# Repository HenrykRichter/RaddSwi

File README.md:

# RaddSwi
This project contains the design files of an automatic MonitorSwitch add-on for the Amiga Flickerfixer [Multifix AGA](https://gitlab.com/MHeinrichs/multifix-aga) by Matthias Heinrichs.
The key idea of using SPDTs for switching between VGA inputs was borrowed from the Ratte Monitor switch by Andre Pfeiffer (hence the title of this project). Also originating from the work of Andre Pfeiffer is the software part. His Amiga utility called switchcontrol is re-used in slightly modified form for this monitor switcher.

Conceptually, a monitor switch is used on Amiga to merge the outputs of Amiga native video (or a Flickerfixer/Scandoubler) and an RTG graphics card to enable the use of a single monitor cable, where the relevant signal is passed through to the monitor. For that purpose, a combination of hard- and software is necessary. 

By default, RaddSwi will pass the native Amiga signal to the monitor. As soon as the software utility detects an active RTG screen, it will generate a signal that instructs the monitorswitch to patch the RTG outputs from the graphics card through. Please see below for differences between the classic Ratte Switch and this approach.

The output of the multiplexed signal can be obtained from the regular VGA connector of the Multifix AGA.

## Hardware notes 
The obvious prerequisite for this solution is a working Multifix AGA. 
This project consists of two PCBs, the switch and a PLCC44 adapter for the switching input signal. 
The PLCC44 adapter for U300 in Amiga 4000 computers requires an 1x4 angled pin strip and an SMD PLCC44 socket. For operation in Amiga2000/3000 computers, please refer to my other projects for a DIP CIAB Adapter.

The components for the switch are listed below:
- 1x STM AV340TTR (Mouser: 511-STMAV340TTR)
- 2x TS5A3159 (Mouser: 595-TS5A3159QDBVRQ1)
- 1x 2x5 R/A shrouded pin header .1" (Mouser: 798-HIF3FC10PA254DS1)
- 1x 2x7 Socket strip vertical .1"
- 1x 10k 0603
- 2x FB 120Ohms@100 MHz
- 3x 100nF 0603
- 1x 10uF 0805
- 1x 1x3 R/A pin header

The switch is supposed to be mounted upside-down on the 2x7 pin strip of the Multifix AGA. Three additional connections are required: 5V, GND and the switch signal. Probably the best option for a stable power supply is the programming header of the MultiFix AGA (JTAG), where Pin 2 carries GND and Pin 4 +5V. The Switch signal connects to CIAB, either DTR or (classic RatteSwitch) CTS.

I'd suggest to go for DTR instead of CTS, since this way is friendlier to the ICs involved. CTS is normally set to input in Amiga computers, where the relevant signal from the serial port is going through an MC1489. Using that pin as output on the CIA will have the CSG8520 pin 8 and the MC1489 pin 6 at odds with each other. That's why this project uses DTR as switching signal, whose state is available both internally (CIAB) and externally (RS232 DB25).

The third piece of hardware needed is the connection between the RTG graphics card and the switcher. The 2x5 connector on raddswi will need analog R,G,B,HSync,VSync and AGND supplied. A typical generic approach is to adapt a short VGA cable for this purpose. Please have a look into the Pics/ subfolder, where the respective connections between a VGA cable and the 2x5 input header are depicted.

## Software notes
Select the SwitchControl binary matching your connection (DTR or CTS), copy it to C: on your Amiga's harddrive and modify your s:user-startup or s:startup-sequence. The only addition to one of the files (preferably s:user-startup) is a line that reads

C:SwitchControl

Important: SwitchControl needs to be started after the Monitor driver(s), thus in s:user-startup or late in s:startup-sequence. 

## Pictures

## License
The PCB, it's design files and all support code are licensed as [CC BY NC SA](https://creativecommons.org/licenses/by-nc-sa/4.0/deed.en).

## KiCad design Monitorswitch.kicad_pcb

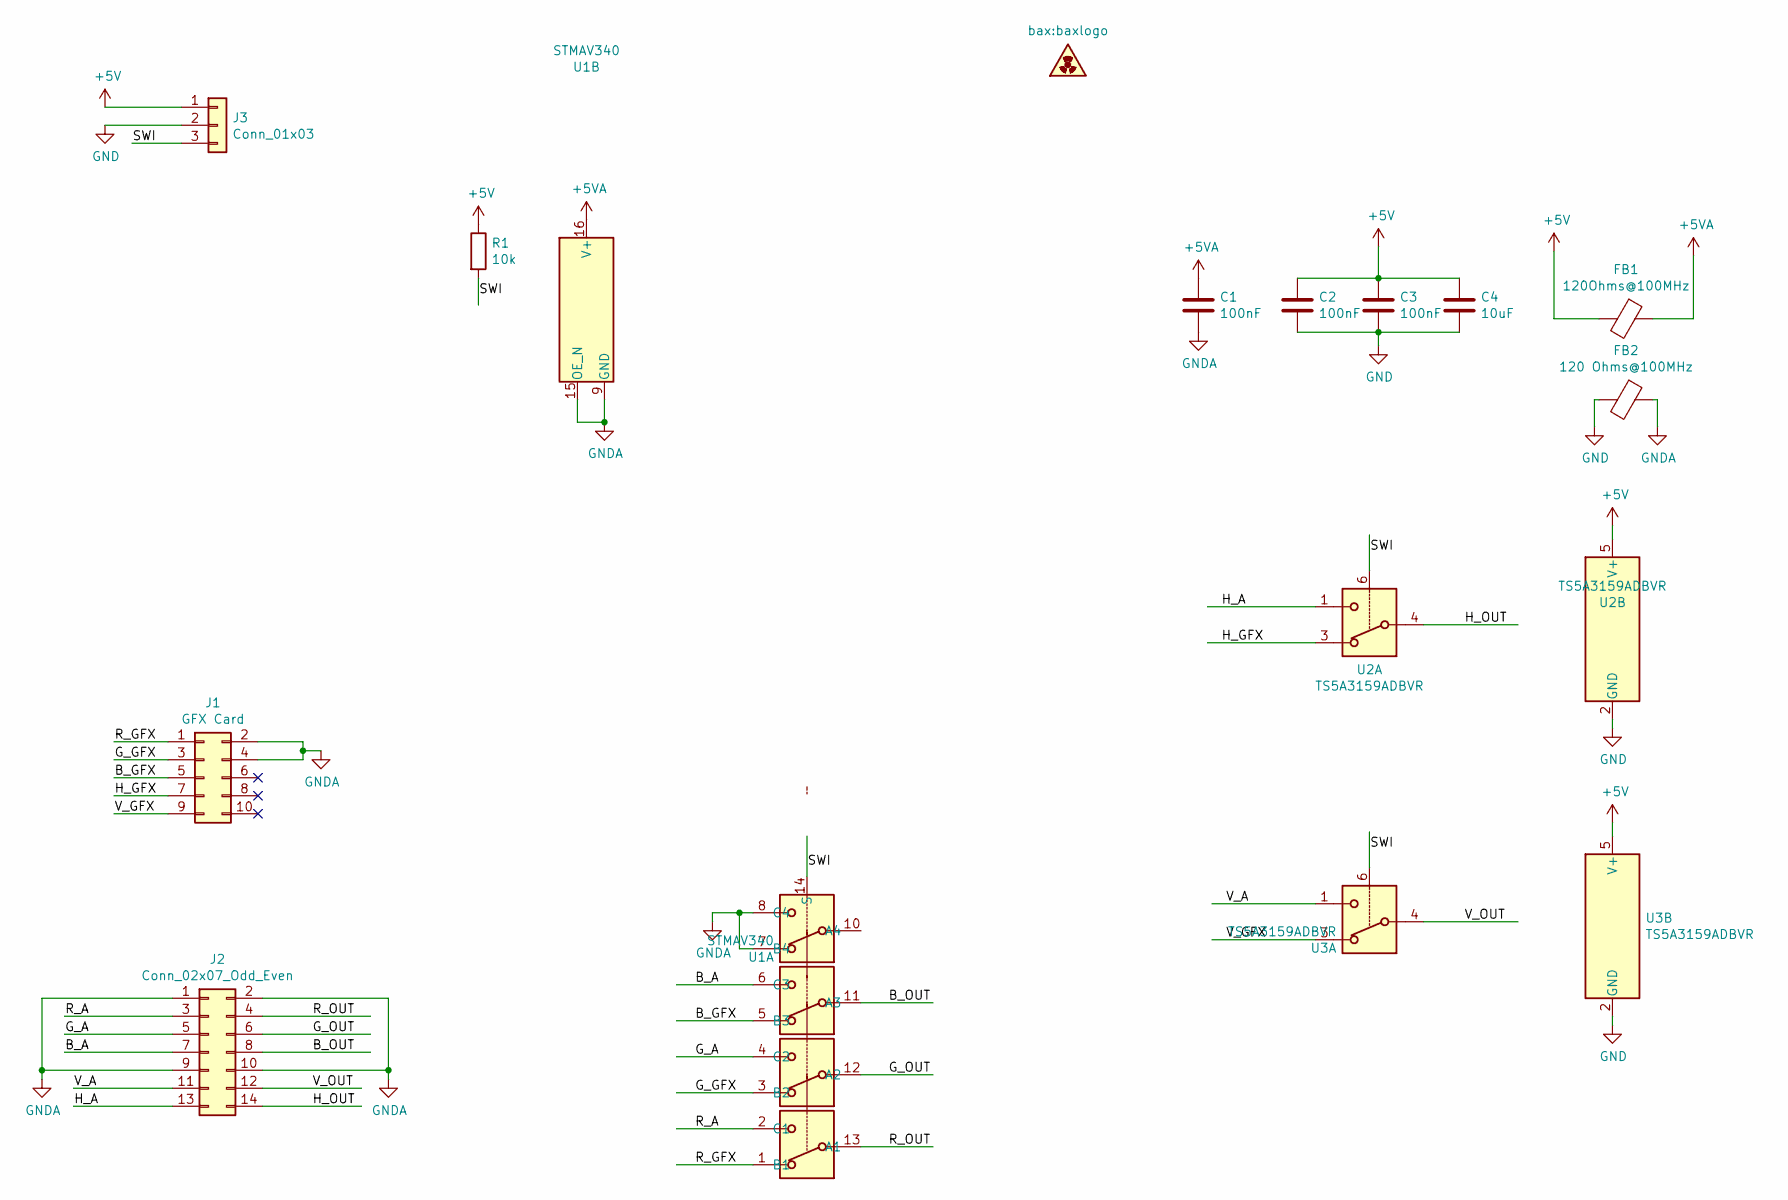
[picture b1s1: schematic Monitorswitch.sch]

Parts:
C1, C2, C3: 100nF; C_0603_1608Metric_Pad1.05x0.95mm_HandSolder
C4: 10uF; C_0805_2012Metric_Pad1.15x1.40mm_HandSolder
FB1: 120Ohms@100MHz; R_0603_1608Metric_Pad1.05x0.95mm_HandSolder
FB2: 120 Ohms@100MHz; R_0603_1608Metric_Pad1.05x0.95mm_HandSolder
J1: GFX Card; IDC-Header_2x05_P2.54mm_Horizontal
J2: Conn_02x07_Odd_Even; PinSocket_2x07_P2.54mm_Vertical
J3: Conn_01x03; PinSocket_1x03_P2.54mm_Horizontal
R1: 10k; R_0603_1608Metric_Pad1.05x0.95mm_HandSolder
U1: STMAV340; TSSOP-16_4.4x5mm_P0.65mm
U2, U3: TS5A3159ADBVR; SOT-23-6

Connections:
+5V: C2.1, C3.1, C4.1, FB1.2, J3.1, R1.1, U2.5 (V+), U3.5 (V+)
+5VA: C1.1, FB1.1, U1.16 (V+)
/B_A: J2.7, U1.6 (C3)
/B_GFX: J1.5, U1.5 (B3)
/B_OUT: J2.8, U1.11 (A3)
/G_A: J2.5, U1.4 (C2)
/G_GFX: J1.3, U1.3 (B2)
/G_OUT: J2.6, U1.12 (A2)
/H_A: J2.13, U2.1
/H_GFX: J1.7, U2.3
/H_OUT: J2.14, U2.4
/R_A: J2.3, U1.2 (C1)
/R_GFX: J1.1, U1.1 (B1)
/R_OUT: J2.4, U1.13 (A1)
/SWI: J3.3, R1.2, U1.14 (S), U2.6, U3.6
/V_A: J2.11, U3.1
/V_GFX: J1.9, U3.3
/V_OUT: J2.12, U3.4
GND: C2.2, C3.2, C4.2, FB2.2, J3.2, U2.2 (GND), U3.2 (GND)
GNDA: C1.2, FB2.1, J1.2, J1.4, J2.1, J2.2, J2.9, J2.10, U1.7 (B4), U1.8 (C4), U1.9 (GND), U1.15 (OE_N)

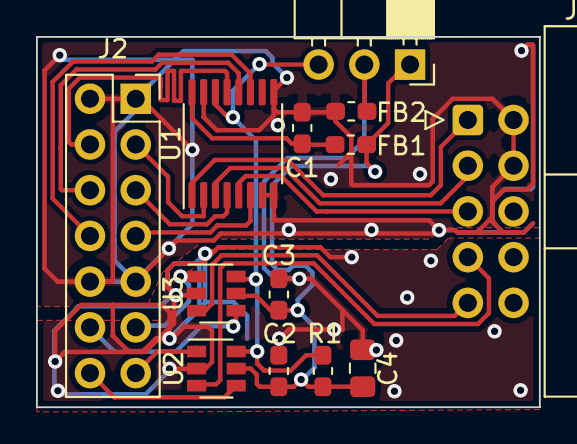
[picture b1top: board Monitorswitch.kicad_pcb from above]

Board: 2 copper layers, 27.9 x 20.6 mm, 13 parts (0 on the bottom side), 20 nets.

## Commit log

2023-03-31 initial upload

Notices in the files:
Monitorswitch.kicad_pcb:
(C) 2022 H. Richter
